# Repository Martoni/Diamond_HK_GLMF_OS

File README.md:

# Diamond_HK_GLMF_OS

Code de mes articles dans les magazines des éditions diamond.

* Pour le github officiel Hackable, [c'est par ici](https://github.com/Hackable-magazine).
* Pour celui de Linux Magazine [par là](https://github.com/GLMF)
* Quand au feu OpenSilicium [c'est ici](https://github.com/OpenSilicium)

# Les articles

* Hackable31: La liberté jusqu'au cœur du processeur avec RISC-V
* Hackable32: Des kits de développement FPGA à moins de 30 €
* Hackable33: Un RISC-V à bas coût pour monitorer votre PC avec LCDproc
* Hackable35: Une carte pilote de LED RGB hackée en kit de développement FPGA à bas coût
* Hackable39: Une sortie VGA pour Game Boy
* Hackable40:
    * Le premier FPGA avec sa chaîne de développement open source
    * Chisel, construire du matériel en langage Scala
* Hackable42: De la preuve formelle en VHDL, librement
* Hackable43: Verilator, le simulateur Verilog le plus rapide du monde
* Hackable44: Transformez votre vieille Game Boy en console de salon HDMI
* Hackable45: Accélérez vos simulations VHDL avec Verilator
* Hackable55:
    * Pimp my LED counter, les performances de l’addition
    * Un oscilloscope à pédale

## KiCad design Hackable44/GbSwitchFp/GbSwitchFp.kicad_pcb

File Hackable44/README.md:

Transformez votre vieille Game Boy en console de salon HDMI
-----------------------------------------------------------

Les sources [Chisel](https://www.chisel-lang.org/) de l'article se trouvent sur
le dépot github [GbHdmi](https://github.com/Martoni/GbHdmi).

Les sources [Kicad](https://www.kicad.org/) (6.0) du PCB se trouvent quand à
elles dans le répertoire `GbSwitchFp`. On y trouve également les fichier
[FreeCad](https://www.freecadweb.org/) nécessaires pour la découpe laser du
support et du capot.

Les explications complémentaires en français sont donné dans le fichier
[COMMENT_FAIRE.md](https://github.com/Martoni/Diamond_HK_GLMF_OS/blob/master/Hackable44/COMMENT_FAIRE.md) et en globish dans [HOWTO.md](https://github.com/Martoni/Diamond_HK_GLMF_OS/blob/master/Hackable44/HOWTO.md)

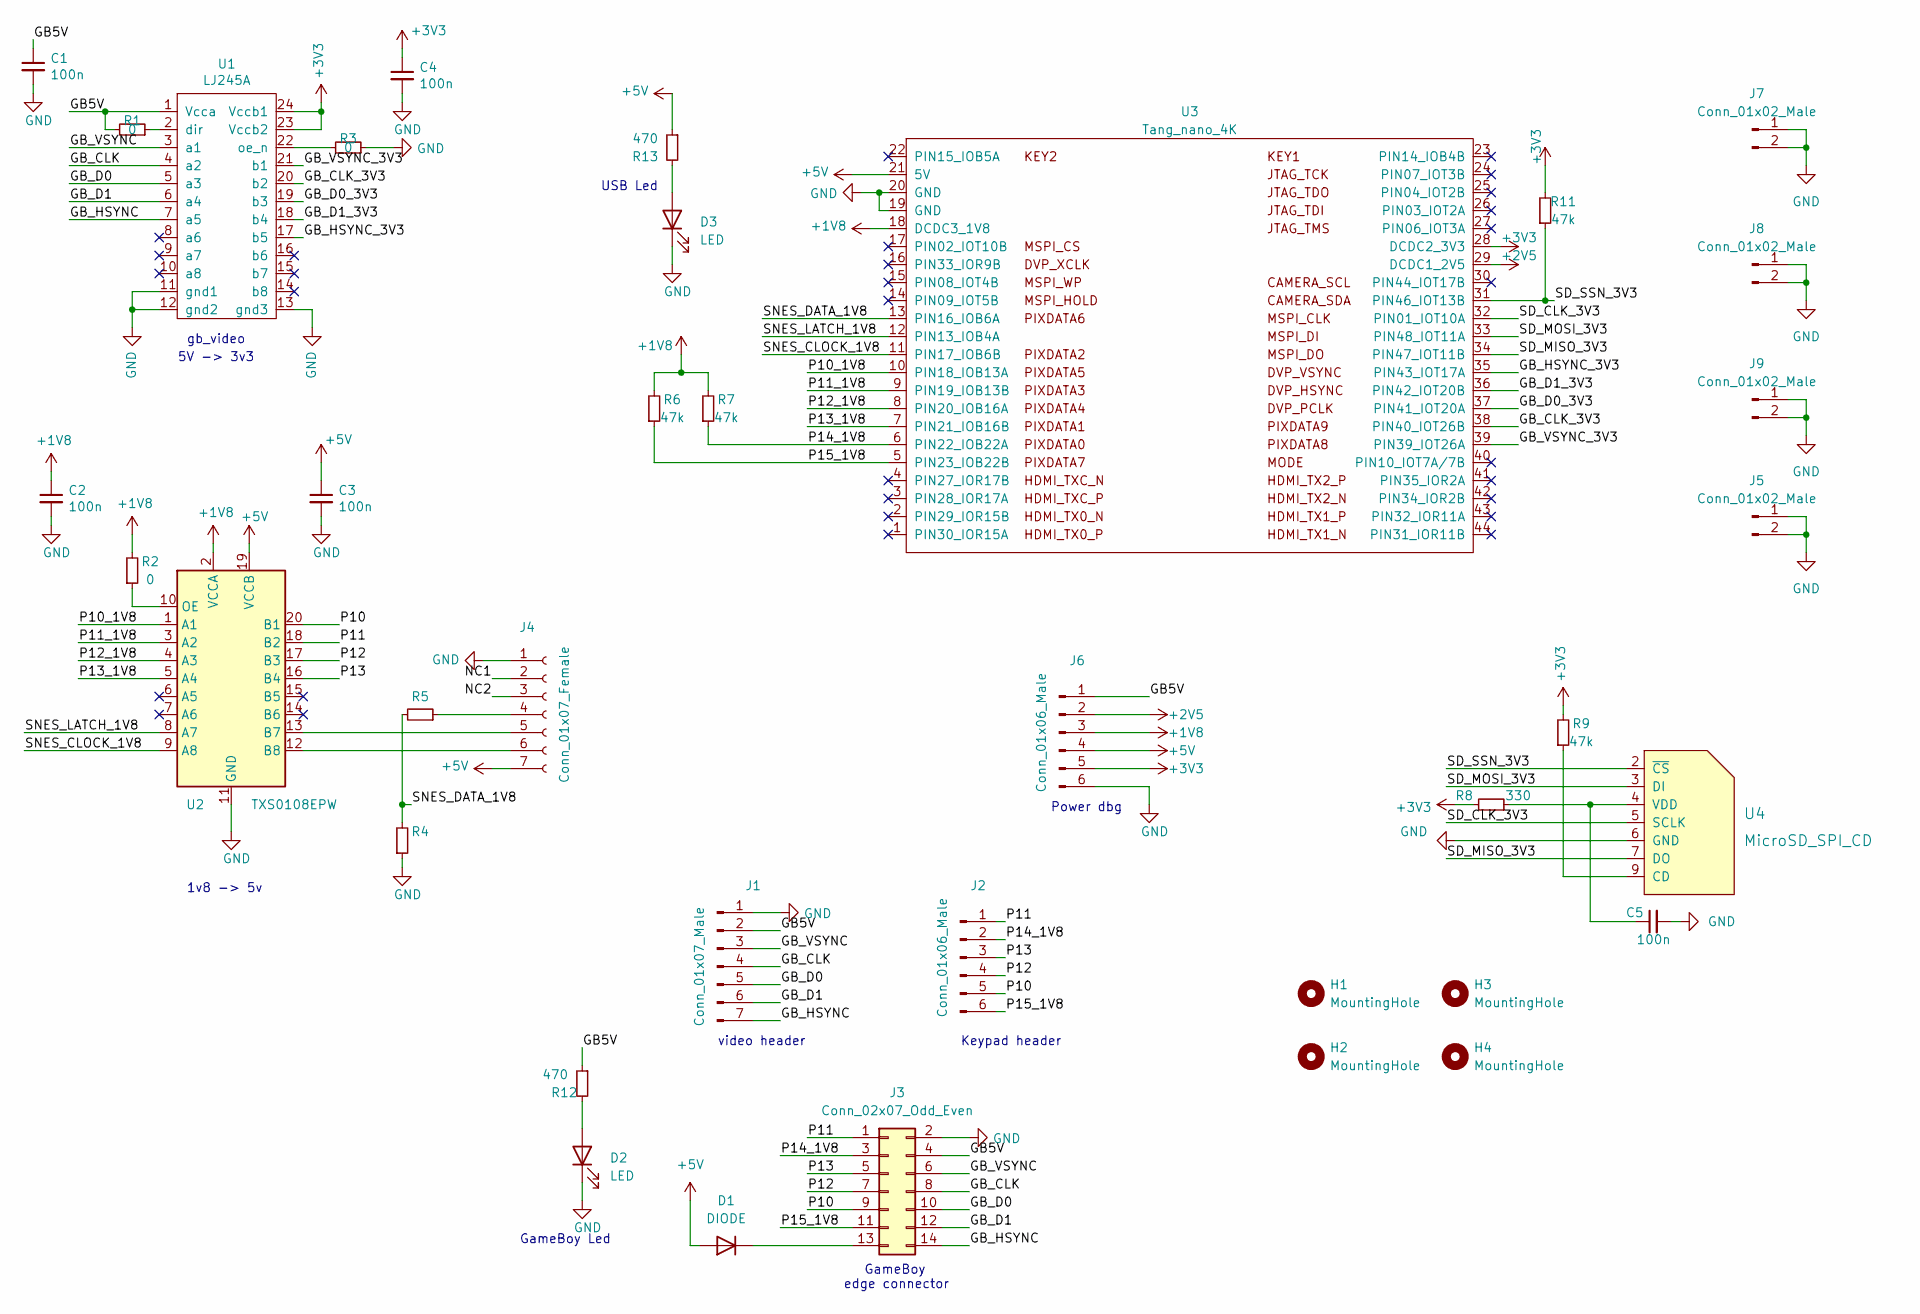
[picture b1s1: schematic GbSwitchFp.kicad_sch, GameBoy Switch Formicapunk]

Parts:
C1, C2, C3, C4, C5: 100n; C_0603_1608Metric
D1: DIODE; D_SOD-123
D2, D3: LED; LED_1206_3216Metric
H1, H2, H3, H4: MountingHole; MountingHole_3.2mm_M3
J1: Conn_01x07_Male; PinHeader_1x07_P2.54mm_Vertical
J2, J6: Conn_01x06_Male; PinHeader_1x06_P2.54mm_Vertical
J3: Conn_02x07_Odd_Even; EDGE_14PIN_254
J4: Conn_01x07_Female; SNES_7PAD
J5, J7, J8, J9: Conn_01x02_Male; PinHeader_1x02_P2.54mm_Vertical
R1, R2, R3: 0; R_0603_1608Metric
R4, R5: R_0603_1608Metric
R6, R7, R9, R11: 47k; R_0603_1608Metric
R8: 330; R_0603_1608Metric
R12, R13: 470; R_0603_1608Metric
U1: LJ245A; TSSOP-24_4.4x7.8mm_P0.65mm
U2: TXS0108EPW; TSSOP-20_4.4x6.5mm_P0.65mm
U3: Tang_nano_4K
U4: MicroSD_SPI_CD; GCT-MEM2055-00-190-01-A

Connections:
+1V8: C2.1, J6.3, R2.2, R6.2, R7.2, U2.2 (VCCA), U3.18 (DCDC3_1V8)
+2V5: J6.2, U3.29 (DCDC1_2V5)
+3V3: C4.1, J6.5, R8.2, R9.2, R11.2, U1.23 (Vccb2), U1.24 (Vccb1), U3.28 (DCDC2_3V3)
+5V: C3.1, D1.2 (A), J4.7, J6.4, R13.1, U2.19 (VCCB), U3.21 (5V)
/GB5V: C1.1, J1.2, J3.4, J6.1, R1.2, R12.1, U1.1 (Vcca)
/GB_CLK: J1.4, J3.8, U1.4 (a2)
/GB_CLK_3V3: U1.20 (b2), U3.38 (PIN40_IOT26B)
/GB_D0: J1.5, J3.10, U1.5 (a3)
/GB_D0_3V3: U1.19 (b3), U3.37 (PIN41_IOT20A)
/GB_D1: J1.6, J3.12, U1.6 (a4)
/GB_D1_3V3: U1.18 (b4), U3.36 (PIN42_IOT20B)
/GB_HSYNC: J1.7, J3.14, U1.7 (a5)
/GB_HSYNC_3V3: U1.17 (b5), U3.35 (PIN43_IOT17A)
/GB_VSYNC: J1.3, J3.6, U1.3 (a1)
/GB_VSYNC_3V3: U1.21 (b1), U3.39 (PIN39_IOT26A)
/NC1: J4.2
/NC2: J4.3
/P10: J2.5, J3.9, U2.20 (B1)
/P10_1V8: U2.1 (A1), U3.10 (PIN18_IOB13A)
/P11: J2.1, J3.1, U2.18 (B2)
/P11_1V8: U2.3 (A2), U3.9 (PIN19_IOB13B)
/P12: J2.4, J3.7, U2.17 (B3)
/P12_1V8: U2.4 (A3), U3.8 (PIN20_IOB16A)
/P13: J2.3, J3.5, U2.16 (B4)
/P13_1V8: U2.5 (A4), U3.7 (PIN21_IOB16B)
/P14_1V8: J2.2, J3.3, R7.1, U3.6 (PIN22_IOB22A)
/P15_1V8: J2.6, J3.11, R6.1, U3.5 (PIN23_IOB22B)
/SD_CLK_3V3: U3.32 (PIN01_IOT10A), U4.5 (SCLK)
/SD_MISO_3V3: U3.34 (PIN47_IOT11B), U4.7 (DO)
/SD_MOSI_3V3: U3.33 (PIN48_IOT11A), U4.3 (DI)
/SD_SSN_3V3: R11.1, U3.31 (PIN46_IOT13B), U4.2 (~CS)
/SNES_CLOCK_1V8: U2.9 (A8), U3.11 (PIN17_IOB6B)
/SNES_DATA_1V8: R4.2, R5.2, U3.13 (PIN16_IOB6A)
/SNES_LATCH_1V8: U2.8 (A7), U3.12 (PIN13_IOB4A)
GND: C1.2, C2.2, C3.2, C4.2, C5.2, D2.1 (K), D3.1 (K), J1.1, J3.2, J4.1, J5.1, J5.2, J6.6, J7.1, J7.2, J8.1, J8.2, J9.1, J9.2, R3.1, R4.1, U1.11 (gnd1), U1.12 (gnd2), U1.13 (gnd3), U2.11 (GND), U3.19 (GND), U3.20 (GND), U4.6 (GND)
unnamed: D2.2 (A), R12.2
unnamed: D3.2 (A), R13.2
unnamed: D1.1 (K), J3.13
unnamed: J4.4, R5.1
unnamed: R1.1, U1.2 (dir)
unnamed: R2.1, U2.10 (OE)
unnamed: R3.2, U1.22 (oe_n)
unnamed: C5.1, R8.1, U4.4 (VDD)
unnamed: R9.1, U4.9 (CD)
unnamed: J4.6, U2.12 (B8)
unnamed: J4.5, U2.13 (B7)

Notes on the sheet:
video header
GameBoy Led
Power dbg
GameBoy edge connector
1v8 -> 5v
gb_video
Keypad header
USB Led
5V -> 3v3

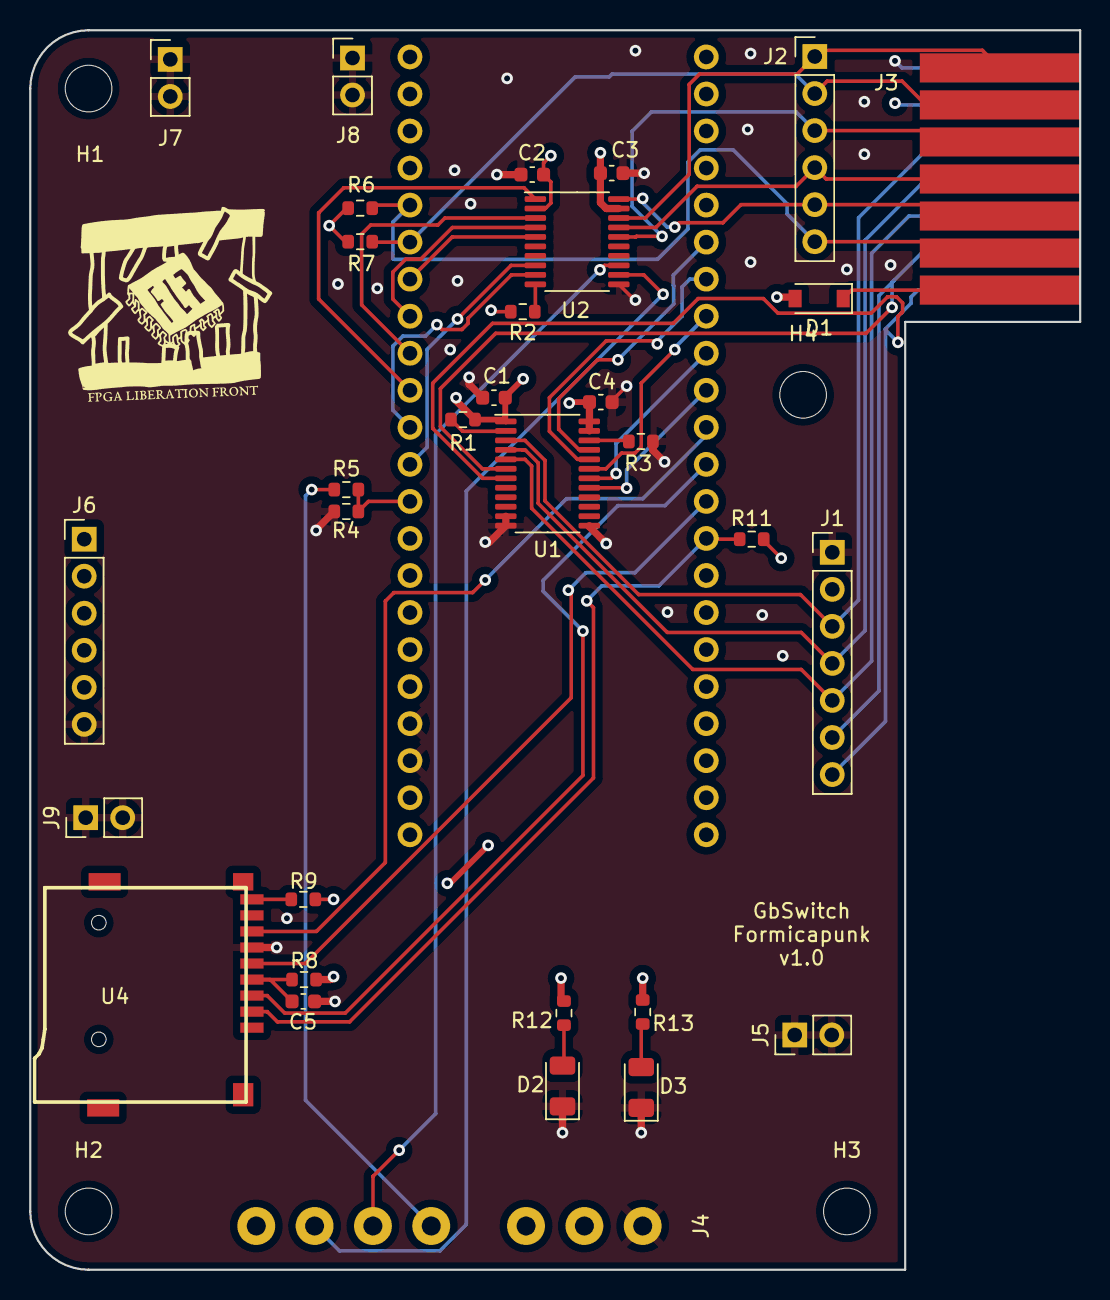
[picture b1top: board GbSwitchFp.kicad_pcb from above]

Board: 4 copper layers, 72.0 x 85.0 mm, 37 parts (1 on the bottom side), 44 nets.

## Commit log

2019-10-07 Hackable31: La liberté jusqu'au cœur du processeur avec RISC-V
2020-01-11 Hackable32: ajout des fichiers pour le icestick
2020-01-11 Hackable32: ajout du schéma de synthèse/placement/routage
2020-01-11 Hackable32: des fichiers pour le fireant
2020-01-11 licheetang: ajout des fichiers
2020-01-11 Hackable32: ajout des fichiers pour le licheetang
2020-01-11 adding link to official github
2020-10-27 HK33 code link
2020-10-27 HK35 code link
2021-10-04 adding HK39 code links
2021-11-11 pre-commit du code de l'article futur HK41?
2021-12-22 adding reference to HK40 articles
2022-03-06 move vhdl psl article in hackable42
2022-07-23 Hackable43: ajout des sources en référence de l'article verilator
2022-09-03 Hackable44: adding document and sources
2022-09-03 Hackable44: adding kicad files
2022-09-03 Hackable44: instructions
2022-09-03 Update README.md
    nitpicks
2022-09-28 adding connector pinout
2022-10-29 Hackable 45: Accélérez vos simulations VHDL avec Verilator
2022-11-03 ajout des titres d'article dans chaque magasines
2024-07-14 Liens vers les sources des articles de Hackable55
2025-12-17 nitpick
